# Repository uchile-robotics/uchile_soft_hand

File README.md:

# uchile_soft_hand
PCB and Firmware for uchile robotics soft hands.

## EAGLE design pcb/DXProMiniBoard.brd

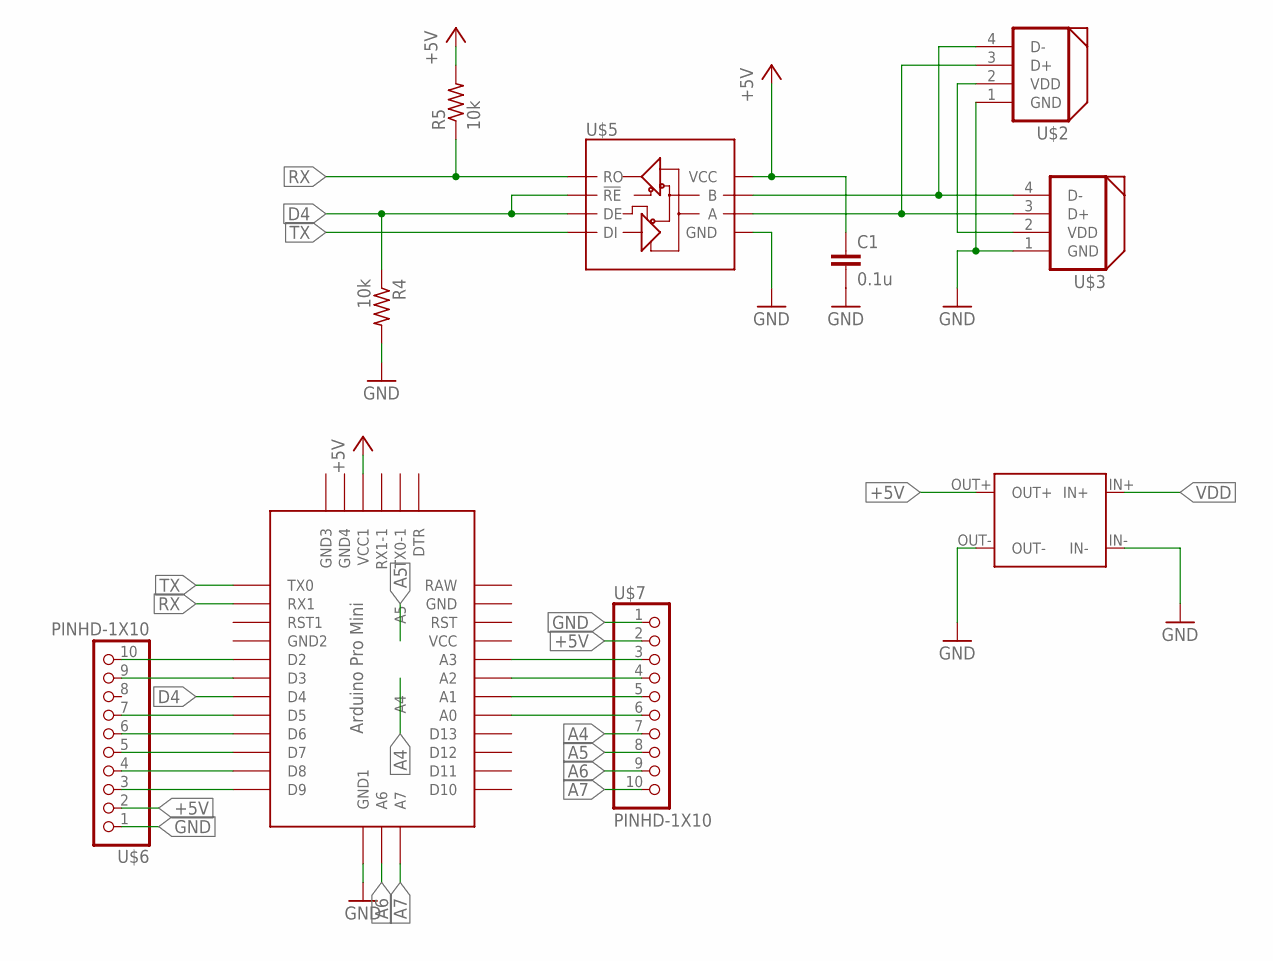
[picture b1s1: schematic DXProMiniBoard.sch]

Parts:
C1: 0.1u; C2.5-2
R4, R5: 10k; 0207/10
U$1: MH-MINI-360MH; MH-MINI-360
U$2, U$3: DYNAMIXEL_RS485; DYNAMIXEL_SPOX_04
U$4: ABK-PRO-MINI
U$5: SN75176B; DIL08
U$6, U$7: PINHD-1X10; 1X10-BIG

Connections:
+5V: C1.1, R5.2, U$1.OUT+, U$4.VCC1, U$5.8 (VCC), U$6.2, U$7.2
A4: U$4.A4, U$7.7
A5: U$4.A5, U$7.8
A6: U$4.A6, U$7.9
A7: U$4.A7, U$7.10
D4: R4.1, U$4.D4, U$5.2 (!RE), U$5.3 (DE)
GND: C1.2, R4.2, U$1.IN-, U$1.OUT-, U$2.1 (GND), U$3.1 (GND), U$4.GND4 (GND1), U$5.5 (GND), U$6.1, U$7.1
unnamed: U$2.4 (D-), U$3.4 (D-), U$5.7 (B)
unnamed: U$2.3 (D+), U$3.3 (D+), U$5.6 (A)
unnamed: U$4.D2, U$6.10
unnamed: U$4.D3, U$6.9
unnamed: U$4.D5, U$6.7
unnamed: U$4.D6, U$6.6
unnamed: U$4.D7, U$6.5
unnamed: U$4.D8, U$6.4
unnamed: U$4.D9, U$6.3
unnamed: U$4.A3, U$7.3
unnamed: U$4.A2, U$7.4
unnamed: U$4.A1, U$7.5
unnamed: U$4.A0, U$7.6
RX: R5.1, U$4.RX1, U$5.1 (RO)
TX: U$4.TX0, U$5.4 (DI)
VDD: U$1.IN+, U$2.2 (VDD), U$3.2 (VDD)

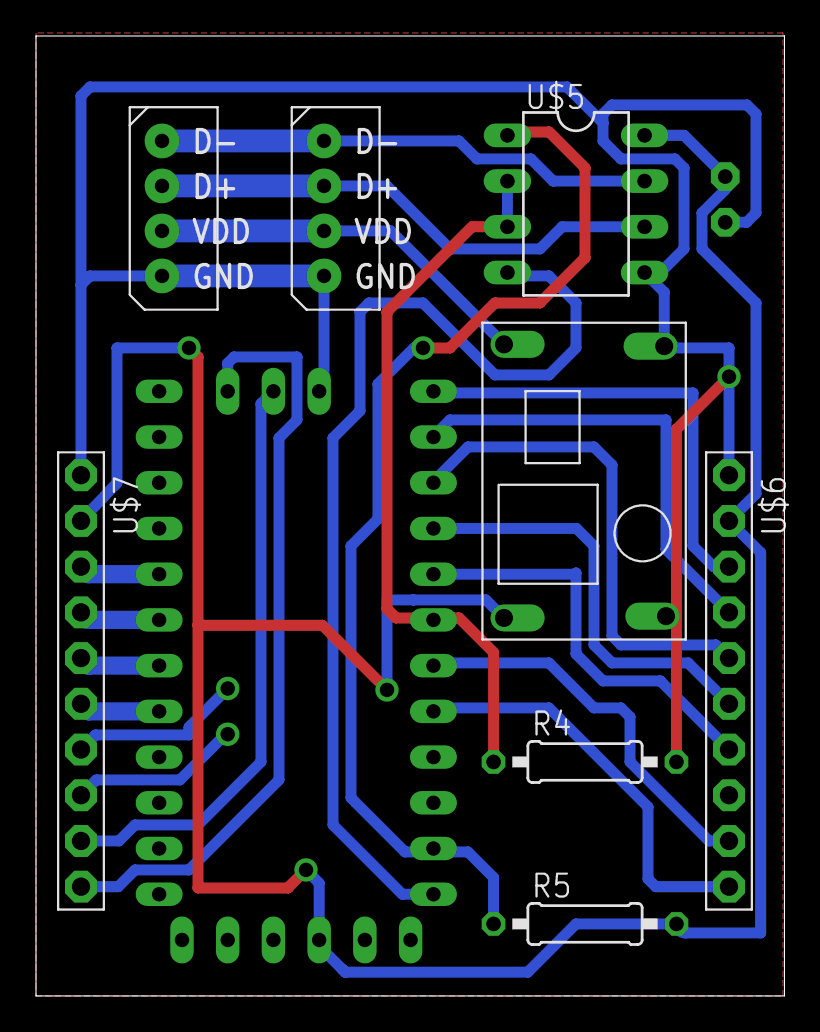
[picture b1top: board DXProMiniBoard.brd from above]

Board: 2 copper layers, 41.6 x 53.3 mm, 10 parts (1 on the bottom side), 23 nets.

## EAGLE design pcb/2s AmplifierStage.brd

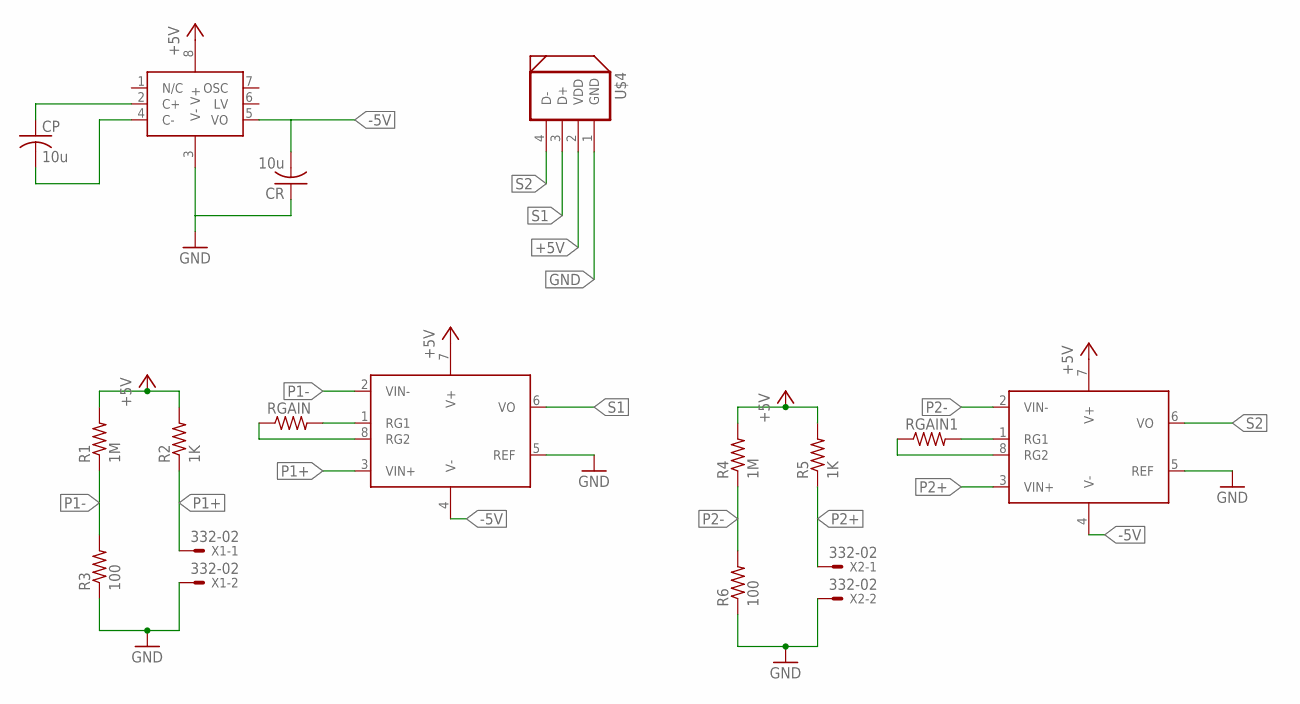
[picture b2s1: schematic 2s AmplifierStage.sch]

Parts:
CP: 10u; C025-050X050
CR: 10u; C025-050X050
R1, R4: 1M; 0207/10
R2, R5: 1K; 0207/10
R3, R6: 100; 0207/10
RGAIN, RGAIN1: R-US_0207/10; 0207/10
U$1: LMC7660DI; DIL08
U$2, U$3: INA128PDIP8; DIL08
U$4: DYNAMIXEL_RS485; DYNAMIXEL_SPOX_04
X1, X2: 332-02

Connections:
+5V: R1.2, R2.2, R4.2, R5.2, U$1.8 (V+), U$2.7 (V+), U$3.7 (V+), U$4.2 (VDD)
-5V: CR.2, U$1.5 (VO), U$2.4 (V-), U$3.4 (V-)
GND: CR.1, R3.1, R6.1, U$1.3 (V-), U$2.5 (REF), U$3.5 (REF), U$4.1 (GND), X1.2, X2.2
unnamed: RGAIN1.2, U$3.1 (RG1)
unnamed: RGAIN1.1, U$3.8 (RG2)
unnamed: CP.1, U$1.2 (C+)
unnamed: CP.2, U$1.4 (C-)
unnamed: RGAIN.2, U$2.1 (RG1)
unnamed: RGAIN.1, U$2.8 (RG2)
P1+: R2.1, U$2.3 (VIN+), X1.1
P1-: R1.1, R3.2, U$2.2 (VIN-)
P2+: R5.1, U$3.3 (VIN+), X2.1
P2-: R4.1, R6.2, U$3.2 (VIN-)
S1: U$2.6 (VO), U$4.3 (D+)
S2: U$3.6 (VO), U$4.4 (D-)

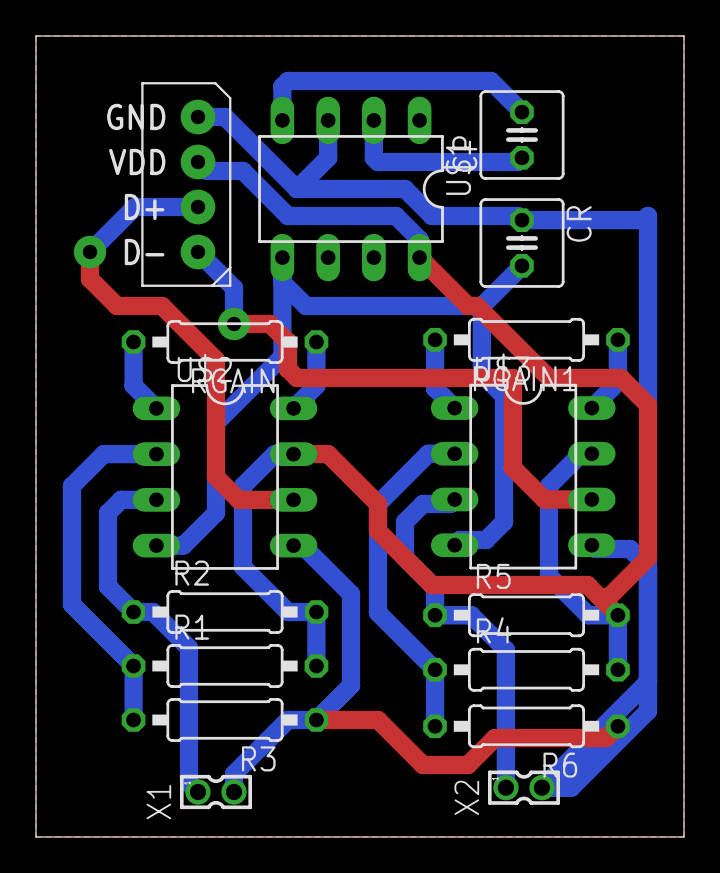
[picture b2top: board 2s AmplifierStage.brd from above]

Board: 2 copper layers, 36.0 x 44.5 mm, 16 parts (0 on the bottom side), 15 nets.

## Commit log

2017-07-16 add Arduino Dx board and soft sensors board
2017-07-16 debug vertion, use arduino Serial3 hardware serial port
2017-07-16 add serial interface, non ros
2017-07-16 rename ...
2017-07-17 add controller, need to create appropriatepackage
2017-07-18 non ros interface working on mega ADK
2017-07-18 add ros package
2017-07-19 Add gripper interface
2017-07-19 Fix publish data
2017-07-19 Add launch file for gripper driver
2017-07-19 working on gripper
